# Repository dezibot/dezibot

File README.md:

# Dezibot4 Lib

## Links to external documentation
* [PDF-Doku Code](https://hardwarelabor.imn.htwk-leipzig.de/dezibot/dezibot.pdf)
* [PDF-Doku Device](https://hardwarelabor.imn.htwk-leipzig.de/dezibot/dezibot-4doku.pdf)

## Link to Software
* [Library](https://github.com/dezibot/dezibot)

## Introduction

The project focuses on the software for the Dezibot4 robot and its use in the classroom.<br>
It includes libraries for use by students as well as guides for teachers. The hardware of the robot is not part of the project.<br>
The libraries and example programs are available under the GPL and are accessible as a repository.<br>
It is ment to serve as an Arduino-Library.<br> 
Therefore the rules for arduinolibrary develop apply:<br>

* [Styleguide](https://docs.arduino.cc/learn/contributions/arduino-library-style-guide)
* [Libraryspecification](https://arduino.github.io/arduino-cli/0.35/library-specification/)
* [Submission-requirements](https://github.com/arduino/library-registry/blob/main/FAQ.md#submission-requirements)

In the following the most important points and custom conventions are introduced.

## Code Conventions

### Don't pass reference

To allow easy usability for users not familier with C++, prevent passing around references. It is better to use
accessmethods

### Naming

* methods are named in lowerCamelCase
* classes are named in UpperCamelCase
* folders containing components are named in lowerCamelCase
* methods are named in lowerCamelCase
* constants are named in ALL_CAPS_SNAKE_CASE

### Bytestream

Every class that implements Byte-Based Communication needs to implement the Arduino Streaminterface

### Components

Every component has a single .h file and one or more .cpp files.<br>
Every component is placed in a seperate folder under src/ that is named equvivalent to the class.
The minimal structure of any .h file is<br>

```c++
#ifndef ClassName_h
#define ClassName_h
class ClassName{

};
#endif //ClassName_h
```

## Design Paradigm

During desgin, the Dezibot isn't describe using it's part but instead it's functionality. Under the top-level
Dezibotclass, there is a class for every functionality of the robot. Each of that classes consists of two parts.

### Part Instances

Each component contains instances of every Robotpart that is used in that component. For example the Motion component
contains two motorinstances, one for motorEast and one for motorWest.
Using these instances, it is possible to access more specific methods that interacts directly with the component (
configure it, setSpeed,...)

### Abstractions

The components constains abstractions that combines multiple partMethods to ease the usability. For example for the
motioncomponent provides an abstraction for the forwardmovement, that involves two motors and even another component (
MotionDetection)

## Contributing

When contributing to the project please follow the rules below. At first, follow all rules from this readme. Further
rules apply to the usage of git

### Branching

Whenever working on the project, create a new branch from the current state of Develop.
Branches should be named as `prefix/#issueid-shortdescription` where prefix is from {feature,fix,refactor}.<br>
When a branch is ready to be used in production, create a mergerequest.

### Mergerequests

The target of each Mergerequest must be the Develop-Branch. Before the merge, each request must be approved by at least
one person with Owner role.<br>
The approve process should consider especially the documentation, naming, implementation.
When the merge is approved and no more commits are added, the last commit must increment the versionnumber in the
library.properties file, following the rules of [Semantic Versioning](https://semver.org/)

### Commitmessages

Commitmessages must follow
the [gitchangelog](https://github.com/vaab/gitchangelog/blob/master/src/gitchangelog/gitchangelog.rc.reference) pattern.

### Language

The language of the project is American English. That includes in particular but not exclusively:

* Sourcecode
* Commit Messages
* Documentation

A german documentation will be provided but does not replace the english documentation.

### Documentation

Documentation of the Software and Hardware can be found at https://docs.dezibot.de/

#### .h Files

```C++
/**
 * @file Dezibot.h
 * @author your name (you@domain.com)
 * @brief 
 * @date 2023-11-19
 * 
 * @copyright Copyright (c) 2023
 * 
 */

```

In the library, the `.h` files should be included using a relative path.
For instance, in `src/Dezibot.h`, to include `src/motion/Motion.h`, you should write `#include "motion/Motion.h"`.

#### Methods

```C++
/**
 * @brief
 * @param
 * ...
 * @return
 *
 */
```

#### Arduino Settings

* Board: "ESP32-S3-USB-OTG"
* Upload Mode: "UART0 / Hardware CDC"
* USB Mode: "Hardware CDC and JTAG"
* Programmer: "Esptool"

Using `arduino-cli` to compile and upload:
`arduino-cli upload /Users/jo/Documents/Arduino/theSketch -p /dev/cu.usbmodem101 -b esp32:esp32:nora_w10`
`arduino-cli compile /Users/jo/Documents/Arduino/theSketch -p /dev/cu.usbmodem101 -b esp32:esp32:nora_w10`

##### Including Library

Arduino IDE -> Sketch -> Include Library -> add .ZIP Library -> this library

If there is any other error like 'Painless_Mesh' not found, you have to include this library also. 

Arduino IDE -> Sketch -> Manage Library -> Search for missing Library

#### Start from Scratch

It is important, before using any functions of Dezibot, to call ```dezibot.begin()``` once in the setup function.

In the examples folder, a sketch ``start`` is provided, that handles the initialization.

## Third-Party Licenses

This project uses the following third-party libraries:

- `veml6040` (version 0.3.2) by [@thewknd](https://github.com/thewknd) et al.
    - Vishay VEML6040 RGBW color sensor library for Arduino
    - Licensed under the MIT license
    - For more information, see the [library's repository](https://github.com/thewknd/VEML6040/blob/master/LICENSE)

## Credits
### Core Team
- [Hans Felix Haupt](https://www.researchgate.net/profile/Hans-Haupt)
- [Anina Ambra Morgner](https://www.researchgate.net/profile/Anina-Morgner) 
- [Saskia Uta Duebener](https://www.researchgate.net/profile/Saskia-Duebener) 
- [Anton Jacker](https://www.researchgate.net/profile/Anton-Jacker) 
- [Jens Wagner](https://fim.htwk-leipzig.de/fakultaet/personen/professorinnen-und-professoren/jens-wagner) 
### Contributors
[All members who Contibuteted in this Project](./CREDITS.md)

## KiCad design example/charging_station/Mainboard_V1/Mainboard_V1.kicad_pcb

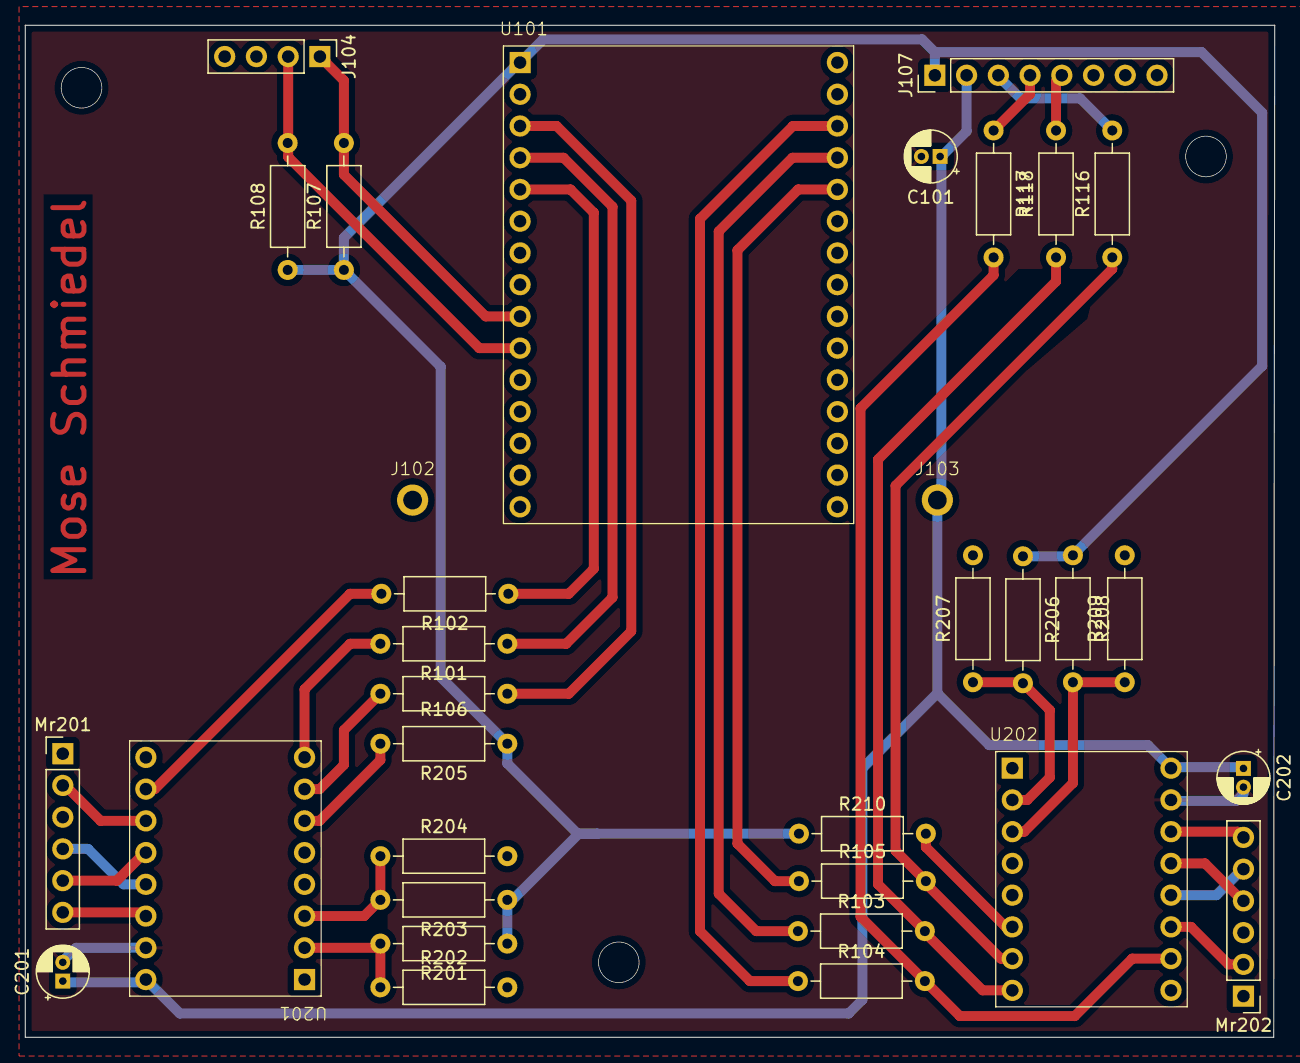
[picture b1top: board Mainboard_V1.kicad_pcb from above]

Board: 2 copper layers, 100.0 x 81.0 mm, 33 parts (0 on the bottom side), 34 nets.

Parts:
C101, C201, C202: 100uF; CP_Radial_D4.0mm_P1.50mm
J102, J103: PogoPin
J104: Conn_01x04_Pin; PinHeader_1x04_P2.54mm_Vertical
J107: Conn_01x08_Pin; PinHeader_1x08_P2.54mm_Vertical
Mr201, Mr202: Stepper_Motor_unipolar_6pin; PinHeader_1x06_P2.54mm_Vertical
R101, R102, R103, R104, R105, R106, R107, R108, R116, R117, R118, R201, R202, R203, R204, R205, R206, R207, R208, R209, R210: 1k; R_Axial_DIN0207_L6.3mm_D2.5mm_P10.16mm_Horizontal
U101: ESP32-WROOM-32; diymore-ESP32-WROOM-32-Devboard
U201, U202: DRV8834; Polulu_DRV8834

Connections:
/DIR_LEFT: R101.2, U201.8 (DIR)
/DIR_RIGHT: R103.2, R118.1, U202.8 (DIR)
/SCL: J104.2, R108.2, U101.10 (D19)
/SDA: J104.1, R107.2, U101.9 (D18)
/STEP_LEFT: R106.2, U201.7 (STEP)
/STEP_RIGHT: R105.2, R116.1, U202.7 (STEP)
/Stepper Motors/~SLEEP_LEFT: R205.2, U201.6 (~SLEEP)
/Stepper Motors/~SLEEP_RIGHT: R210.2, U202.6 (~SLEEP)
/~FAULT_LEFT: R102.2, U201.15 (~FAULT)
/~FAULT_RIGHT: R104.2, R117.2, U202.15 (~FAULT)
GND: C101.2, C201.2, C202.2, U201.10 (GND), U202.10 (GND)
unnamed: J107.3, R116.2
unnamed: J107.4, R117.1
unnamed: J107.5, R118.2
unnamed: Mr201.5 (-), U201.13 (A1)
unnamed: R101.1, U101.4 (D2)
unnamed: R102.1, U101.5 (D4)
unnamed: R103.1, U101.19 (D12)
unnamed: R104.1, U101.18 (D13)
unnamed: R105.1, U101.20 (D14)
unnamed: R106.1, U101.3 (D15)
unnamed: Mr201.2, U201.14 (A2)
unnamed: Mr201.4, U201.12 (B1)
unnamed: Mr201.6, U201.11 (B2)
unnamed: R201.2, R202.1, U201.2 (M0)
unnamed: R203.2, R204.1, U201.3 (M1)
unnamed: Mr202.5 (-), U202.13 (A1)
unnamed: Mr202.2, U202.14 (A2)
unnamed: Mr202.4 (-), U202.12 (B1)
unnamed: Mr202.6, U202.11 (B2)
unnamed: R206.2, R207.1, U202.2 (M0)
unnamed: R208.2, R209.1, U202.3 (M1)
VBUS: C101.1, C201.1, C202.1, J103.1, J107.2, U201.9 (VMOT), U202.9 (VMOT)
VDD: J107.1, R107.1, R108.1, R201.1, R203.1, R205.1, R206.1, R208.1, R210.1, U101.1 (3V3)

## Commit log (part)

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2024-06-14 initial release
2024-06-14 Added link to software to readme
2024-08-13 chg: dev: introduced methods to start and stop writing datapackages to FIFO
2024-08-13 fix: dev: added statements to turn fifo on only when needed --> fixes other MotionDetection Functions (getOrientation...)
2024-08-16 corrected comments in start/stop fifo
2024-08-16 fix: dev: added call to fifoStop() at the end of motion.stop()
2024-08-31 remove conflict comments
2024-09-04 Example window dressing
2024-10-21 Update README.md
    change link to git
2024-11-04 labyrinthSolver Dateien vorbereitet
2024-11-04 h File begonnen
2024-11-05 Fix color detection library.
2024-11-05 Fix style.
2024-11-05 Add licence attributions.
2024-11-05 Remove unnecessary breaks and void.
2024-11-05 Update library properties.
2024-11-12 Start und Example Dateien initialisiert
2024-11-12 Farbinitilaisierung eingebaut
2024-11-12 Intilaisierung der Farben vereinfacht
2024-11-14 Fix UB in FrequencyFindAFriend
    if all 4 IR sensors report no amplitude, the index for the brightest sensor wont be initialized, often causing a crash
2024-11-18 neue Dezibot ColorDetection eingebaut
2024-11-24 display: fix width-overflow linebreak bug; use i2c command batch
    when a line wraps onto the next, any following scr.println output was indented by 1, caused by overflow incorrectly being calculated using mod 17
2024-11-24 implement Battery class to get charging state/voltage/approx. battery level%
2024-11-25 display: implement faster linebreak without zeroing out remaining pages
2024-11-25 fix arduino ide compatibility by not using constexpr
    hey siri wie alt ist c++11
2024-11-25 properly wrap text line 9 and higher to line 1 etc
2024-11-25 add 'depends' field for arduino; add json for platformio
    Arduino dependency resolution will not work ATM, Dezibot has to be added to the library registry first. PlatformIO works
2024-11-25 fix platformio AsyncTCP ambiguity
2024-11-27 revert new linebreak code; properly restore sd1306 page offset (line idx) after drawing battery
    revert because not blanking the whole row can look weird if line overflowing to line 0 has fewer chars than what was there previously
2024-12-01 MoveTest zeigt Verfolgung der Linie mit Rot Grün Linienienverfolgung
2024-12-02 TODOs added
2024-12-03 Verbessertes Movement
2024-12-03 TODO added
2024-12-09 Lenkung eingebaut rohvariante
2024-12-11 Deadend fertig aber komischer BUG der nicht sein sollte
2024-12-17 Fehler eingegrenzt
2024-12-21 Motor Bug behoben + Test ohne deadendrotation State
2024-12-21 Test ohne deadend
2024-12-23 Refactoring und Getter und Setter vorheriger Konstanten
2024-12-25 Reafctoring und Umbau von enum auf define ints
2024-12-25 Scaling Grün Rot ausgeglichen + Konst Auslagerung
2024-12-25 NormalStand mit Kal. an --> P-Regler verworfen da grün rot Trennung nicht genau genug
2024-12-26 Umbau aus Ino in einzelne cpp und h Dateien
2024-12-26 Neue cpp und h Dateien hinzugefuegt
2024-12-26 deadendRoration durch beschreibende Kommentare ergänzt
2024-12-26 Kalibrierung aktiviert
2024-12-29 calibrated Variablen klein geschrieben
2024-12-29 calibrated Werte klein geschrieben, zweiter Teil vom letzte Commit
2024-12-29 Refactoring nach Arduino Styleguide
2024-12-29 Docs hinzugefügt
2024-12-29 Define in Enum Umstellung
2024-12-29 colorSwitch und invertComparison durch Enum und dessen Methoden getauscht
2024-12-29 add files
2024-12-29 add methods
2024-12-30 Datum angepasst
2024-12-30 add Comments
2025-01-05 change common definition
2025-01-18 fix crossingModel
2025-01-19 temp commit
2025-01-19 fix location
2025-01-19 adjust path
2025-01-20 fix imports
2025-01-22 Added platform.io to project for dependency management
2025-01-22 Added dependencies and sample main file
2025-01-22 Initial draft, updated dependencies
2025-01-25 UML Class chart, modified .gitignore
2025-01-26 Implemented basic webserver, added basic webpages
2025-01-26 Updated UML
2025-01-26 add Setup Method
2025-01-27 Added Logging + LoggingDatabase with blank default implementations, added test-logging into main
2025-01-27 modified .gitignore to properly catch all pio files
2025-01-28 move until marker
2025-01-29 move until marker stand
2025-01-29 adjust exploration
2025-01-30 HTML can now be read from files, changed main page
2025-01-30 implemented example page for live data to test functionality
2025-02-01 gassi geh version
2025-02-02 PID zwischenstand
2025-02-03 ganz gutes PID
2025-02-03 klappt so halbwegs
2025-02-03 geschwindigkeit verringern
    damit er nicht so weit über blau hinweg schießt
2025-02-03 new area when comming frome blue
    so that it gets noticed earlyer without getting found out by trichter
2025-02-03 geschwindigkeit wieder rückgänig
2025-02-04 versuch t1 zu meisten
    nach reset farbe richtig drehen und nach dead end rotation nicht so lange warten
2025-02-05 print out direction
2025-02-05 remove non print changes to get to working state
    only colormode change stayed in
2025-02-05 measure mode to get new values
2025-02-05 lauf Version
2025-02-05 lauffähige version
2025-02-05 controll for helpgull guidance for red or green lfet
2025-02-05 better clear T1 crossings
2025-02-05 more graph printing
2025-02-05 print crossing when found
2025-02-05 speed up so to reach a better postion for detection
2025-02-05 adjust Sensorconfig and reverse speed
2025-02-06 fix bug where iterations are allways reset
2025-02-06 when red is legt tun shorter so to be on green to corect yourself
2025-02-06 old Ordner entfernt
2025-02-06 trigger enabled typo
2025-02-06 trigger Satz ergänzt
2025-02-06 Version Colordetection angehoben
2025-02-06 Zeile entfernt
2025-02-06 Typos
2025-02-06 MaxMager Angabe und alte Dateien entfernt
2025-02-06 manual umschreimbungen
2025-02-06 ZombieCode entfernt
2025-02-06 trigger typo
2025-02-06 Zombie Code
2025-02-06 marker typo
2025-02-06 i variable entfernt
2025-02-06 refactor measure time ausgabe
2025-02-06 Gaolfilled typo
2025-02-07 add documentation
2025-02-07 remove changes from dezibot
2025-02-15 implemented settings page, sensors can be enabled/disabled
2025-02-15 Updated mainpage to use relative urls
2025-02-15 Implemented basic functionality of LiveDataPage
2025-03-09 added some sample loggers, fixed struct order
2025-03-09 timestamp function with relative time instead of absolute
2025-03-09 filestructure refactor
2025-03-09 Added missing functions for livedata sensor values, added Utility class
2025-03-09 Changed display name for sensors in livedata
2025-03-09 Refactors for Logging + Logging setup for various basic functions
2025-03-09 Added missing function calls for colorDetection in livedata
2025-03-12 fixed typo from refactoring
2025-03-12 removed test webserver code that does not belong in this branch
2025-03-12 reverted accidental file removal
2025-03-12 prevent the writing of logs while on livedata page
2025-03-13 webserver now runs on a separat thread
2025-03-13 Implemented Classes for sensors and sensorfunctions
2025-03-13 Changed SettingsPage to render dynamically, depending on existing sensors
2025-03-13 Added missing sensor objects during setup
2025-03-14 changed LiveDataPage to utilize new sensor objects
2025-03-14 refactoring and documentation
2025-03-15 fixed styling, added comments for json formatting
2025-03-15 cleanup of comments
2025-03-22 added LoggingPage to display logs with filtering
2025-03-22 replaced deprecated functions in LiveDataPage
2025-03-22 replaced deprecated functions in SettingsPage
2025-03-22 Updated class diagram
2025-03-22 added style handler for main page, added style css file, added js handler for live data page, added minified js library canvasjs, added some more logging utility
2025-03-22 changed existing loggers to be more consistent
2025-03-22 first attempt at better page reading for larger files (does not work yet)
2025-03-23 Added comments to header files according to dezibot documentation guidelines
2025-03-23 Added comments to source files according to dezibot documentation guidelines
2025-03-23 Added comments
2025-03-24 Added streaming function for file transfer, split livedatapage and main page code into separate files, small main cleanup, added canvasjs implementation for single chart (ambientLight)
2025-03-24 new logDatabase functionality to only return new log entries, working implementation on existing code
2025-03-26 Removed duplicate code. loadLogs() now takes endpoint as parameter to be able to get data from multiple backend functions
2025-03-26 Removed duplicate code for loggingPage endpoints.
2025-03-26 refactor with proper tabulation, slider for chartLimit
2025-03-26 working multi-dataset chart implementation
2025-03-26 refactoring for readability and better code style
2025-03-26 Added fake function for RGB testing
2025-03-26 restructuring of /data/ subfolders, moved all css and js to appropriate files, created handlers for those new files, moved all old handlers from string reading to streaming
2025-03-28 Added generic 404-error page, added handler for 404s, added style
2025-04-08 Renamed example folder to examples for ArduinoLibary integration
2025-04-08 added dependenies to properties file for automatic impoft in Arduino Libary
2025-04-25 update readme to contain credits
2025-04-25 added credits
2025-10-09 Change runner to self-hosted for sync job
2025-10-09 Add test build for gitlab tests
2025-10-09 Revert "Added GitHub Self hosted action"
2025-10-09 Add build and hardware stages to CI pipeline
2025-10-09 Disable deploy stage in .gitlab-ci.yml
    Comment out the deploy stage and its associated script in the GitLab CI configuration.
2025-10-10 Update test stage echo message in CI configuration
2025-10-10 Modify test stage echo message in CI configuration
    Updated test stage to echo 'Synced' instead of the previous message.
2025-10-12 Add Arduino test script and update CI configuration
2025-10-12 Add dependency on compile job for sync and remove Arduino CLI installation step
2025-10-12 Update comments for dependency installation and add dezibot installation step
2025-10-12 update timeout
2025-10-12 added update to libarie
2025-10-12 fixing compile and dezibot instal
2025-10-12 allways test on latest core
2025-10-12 enabled unsafe
2025-10-13 try update .ino path
2025-10-13 please!
2025-10-13 added one debug
2025-10-13 try over rename the test file
2025-10-13 list core
2025-10-13 update fqbn
2025-10-17 added first test
2025-10-17 fixing but with output path
2025-10-17 fixed path
2025-10-17 updated failure in first test
2025-10-17 use newer version of upload artifact
2025-10-17 tryed other tty port
2025-10-17 port
2025-10-17 poer ttys2
2025-10-17 connected dezibot
2025-10-17 set timeout to ms
2025-10-17 remove some fo tests
2025-10-17 other version to monitor
2025-10-17 readded artifact
2025-10-18 tryed more config
2025-10-18 refactor: update board options for compile and upload steps in RGB LED Test
2025-10-18 additional debug
2025-10-18 updated, so hopefuly it works
2025-10-18 changed artefact generation
2025-10-19 try to log
2025-10-19 added log flag to serial monitor
2025-10-19 remove timeout as test
2025-10-19 tryed other form to read the log
2025-10-19 again with screen, prob. will end it throu cleanup
2025-10-19 added sleep aftewr screen
2025-10-19 fix: redirect screen output to log file instead of using append
2025-10-19 try other version
2025-10-19 increased timeout
2025-10-19 varey timeout again
2025-10-19 rearrange order
2025-10-19 please
2025-10-19 prevent code 130 hopefully
2025-10-20 added test result
2025-10-20 added all test
2025-10-25 added checkout
2025-10-25 added monitoring
2025-10-25 refactor
2025-10-25 maby?
2025-10-25 try2
2025-10-25 artefact v4
2025-10-25 added pull request
2025-10-25 undo refactoring
2025-10-26 added PR
2025-10-26 remove remove esp32
2025-10-26 update to use variables to test
2025-10-26 updated vars on compile
2025-10-26 added an install and Prepare Script
2025-10-26 updated to use vars
2025-10-26 Try other aproach to get script better reusable
2025-10-26 remove bash shell
2025-10-26 undo monitor as variable
2025-10-28 allwys upload artefact
2025-10-28 added workflow dispatch to test dezibot functionality
2025-11-01 better logs
2025-11-01 diable baterie result
2025-11-02 removed baterie check results
2025-11-03 entfernen von sync testcode
